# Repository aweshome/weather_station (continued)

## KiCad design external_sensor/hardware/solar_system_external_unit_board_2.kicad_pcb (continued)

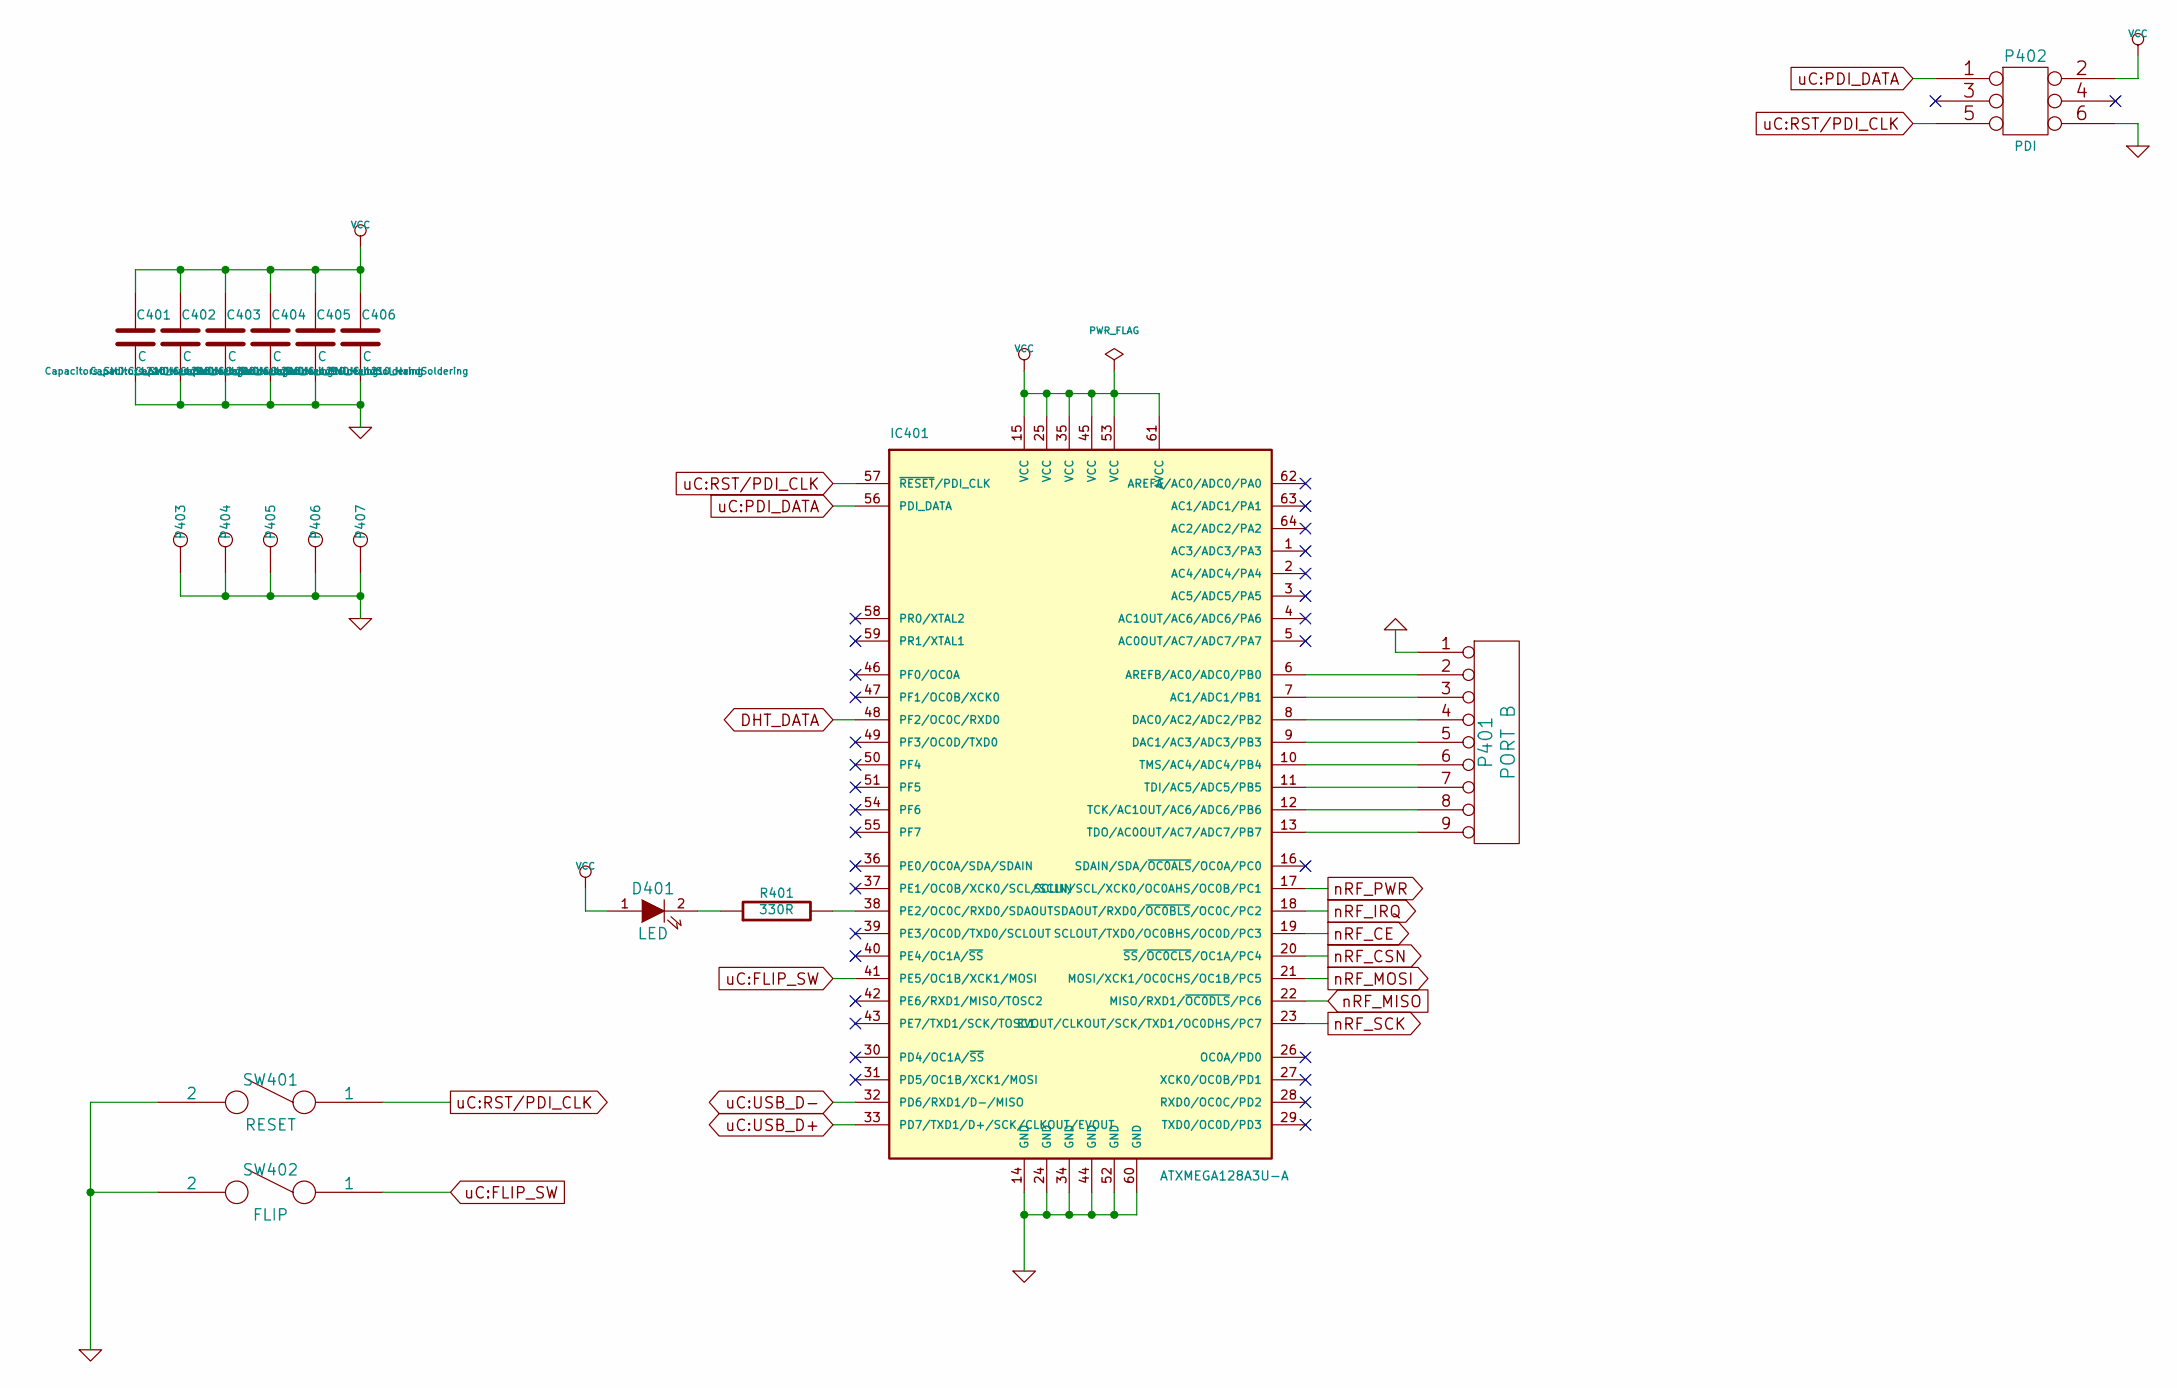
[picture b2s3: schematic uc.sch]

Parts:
C401, C402, C403, C404, C405, C406: C; C_1210_HandSoldering
D401: LED; LED_1206
IC401: ATXMEGA128A3U-A; TQFP-64_14x14mm_Pitch0.8mm
P401: PORT B; Pin_Header_Straight_1x09
P402: PDI; Pin_Header_Straight_2x03
P403, P404, P405, P406, P407: CONN_1; SolderWirePad_single_0-8mmDrill
R401: 330R; R_1206_HandSoldering
SW401: RESET; SW_Tactile_SPST_Angled
SW402: FLIP; SW_Tactile_SPST_Angled

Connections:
DHT_DATA: IC401.48 (PF2/OC0C/RXD0); also elsewhere on the board
GND: C401.2, C402.2, C403.2, C404.2, C405.2, C406.2, IC401.14 (GND), IC401.24 (GND), IC401.34 (GND), IC401.44 (GND), IC401.52 (GND), IC401.60 (GND), P401.1, P402.6, P403.1, P404.1, P405.1, P406.1, P407.1, SW401.2, SW402.2; also elsewhere on the board
unnamed: D401.2 (K), R401.1
unnamed: IC401.6 (AREFB/AC0/ADC0/PB0), P401.2
unnamed: IC401.7 (AC1/ADC1/PB1), P401.3
unnamed: IC401.8 (DAC0/AC2/ADC2/PB2), P401.4
unnamed: IC401.9 (DAC1/AC3/ADC3/PB3), P401.5
unnamed: IC401.10 (TMS/AC4/ADC4/PB4), P401.6
unnamed: IC401.11 (TDI/AC5/ADC5/PB5), P401.7
unnamed: IC401.12 (TCK/AC1OUT/AC6/ADC6/PB6), P401.8
unnamed: IC401.13 (TDO/AC0OUT/AC7/ADC7/PB7), P401.9
unnamed: IC401.38 (PE2/OC0C/RXD0/SDAOUT), R401.2
VCC: C401.1, C402.1, C403.1, C404.1, C405.1, C406.1, D401.1 (A), IC401.15 (VCC), IC401.25 (VCC), IC401.35 (VCC), IC401.45 (VCC), IC401.53 (VCC), IC401.61 (AVCC), P402.2; also elsewhere on the board
nRF_CE: IC401.19 (SCLOUT/TXD0/OC0BHS/OC0D/PC3); also elsewhere on the board
nRF_CSN: IC401.20 (~SS~/~OC0CLS~/OC1A/PC4); also elsewhere on the board
nRF_IRQ: IC401.18 (SDAOUT/RXD0/~OC0BLS~/OC0C/PC2); also elsewhere on the board
nRF_MISO: IC401.22 (MISO/RXD1/~OC0DLS~/PC6); also elsewhere on the board
nRF_MOSI: IC401.21 (MOSI/XCK1/OC0CHS/OC1B/PC5); also elsewhere on the board
nRF_PWR: IC401.17 (SCLIN/SCL/XCK0/OC0AHS/OC0B/PC1); also elsewhere on the board
nRF_SCK: IC401.23 (EVOUT/CLKOUT/SCK/TXD1/OC0DHS/PC7); also elsewhere on the board
uC:FLIP_SW: IC401.41 (PE5/OC1B/XCK1/MOSI), SW402.1
uC:PDI_DATA: IC401.56 (PDI_DATA), P402.1
uC:RST/PDI_CLK: IC401.57 (~RESET~/PDI_CLK), P402.5, SW401.1
uC:USB_D+: IC401.33 (PD7/TXD1/D+/SCK/CLKOUT/EVOUT); also elsewhere on the board
uC:USB_D-: IC401.32 (PD6/RXD1/D-/MISO); also elsewhere on the board

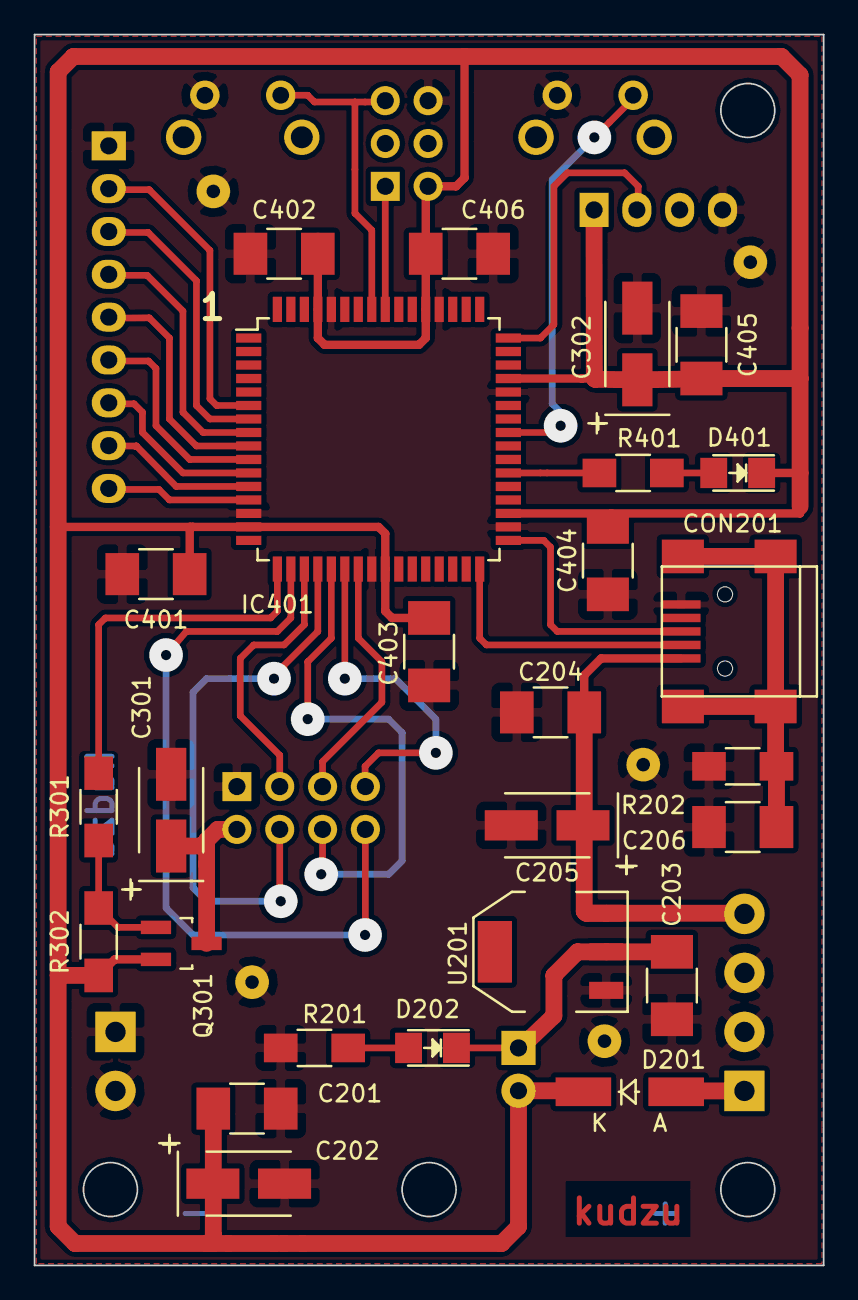
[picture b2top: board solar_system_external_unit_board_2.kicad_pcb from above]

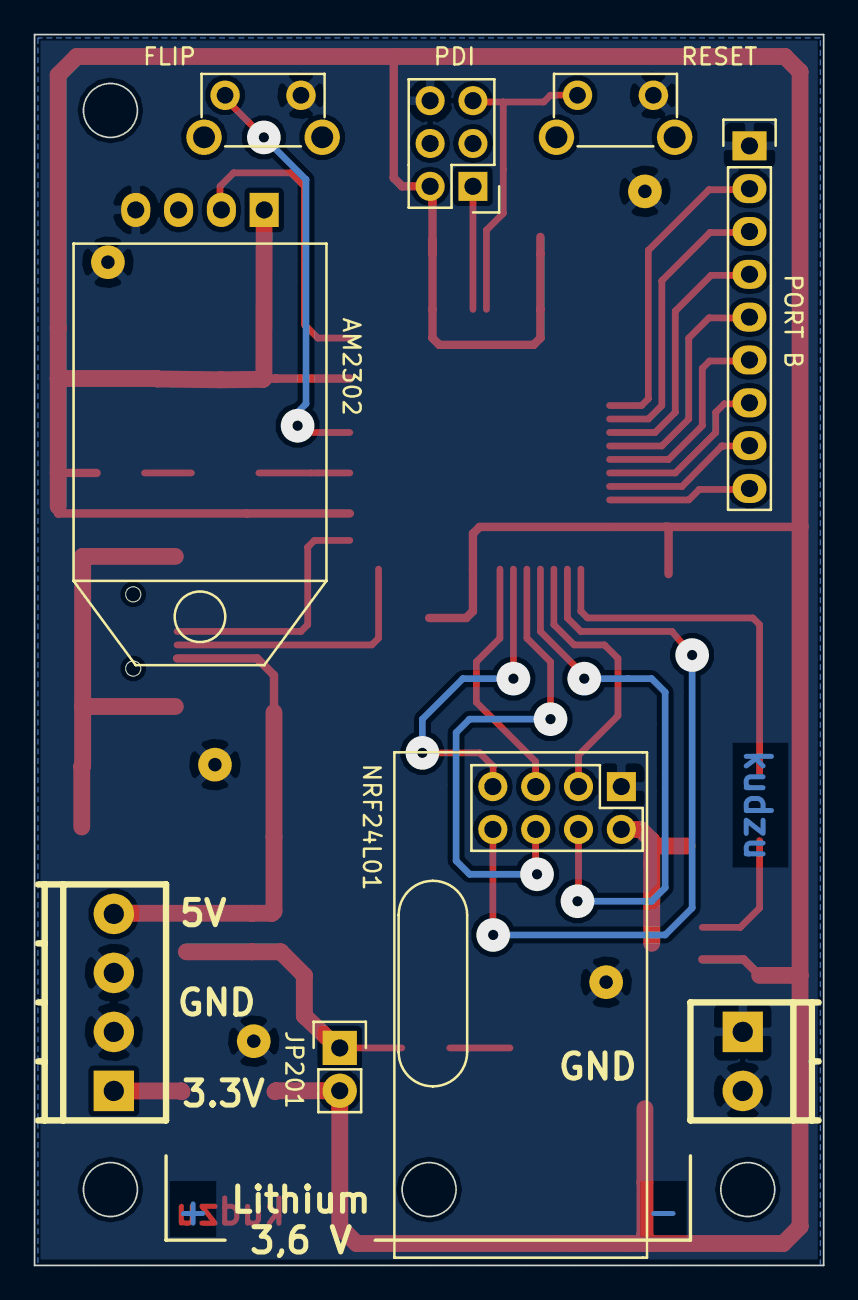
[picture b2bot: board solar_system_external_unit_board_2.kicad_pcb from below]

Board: 2 copper layers, 46.8 x 73.0 mm, 40 parts (9 on the bottom side), 32 nets.

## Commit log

2020-10-13 Add existing files
2020-10-13 Update README.md
    Markdown syntax error
